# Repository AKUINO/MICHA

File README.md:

# MICHA
Modbus Interface to Control Heat and Actuators

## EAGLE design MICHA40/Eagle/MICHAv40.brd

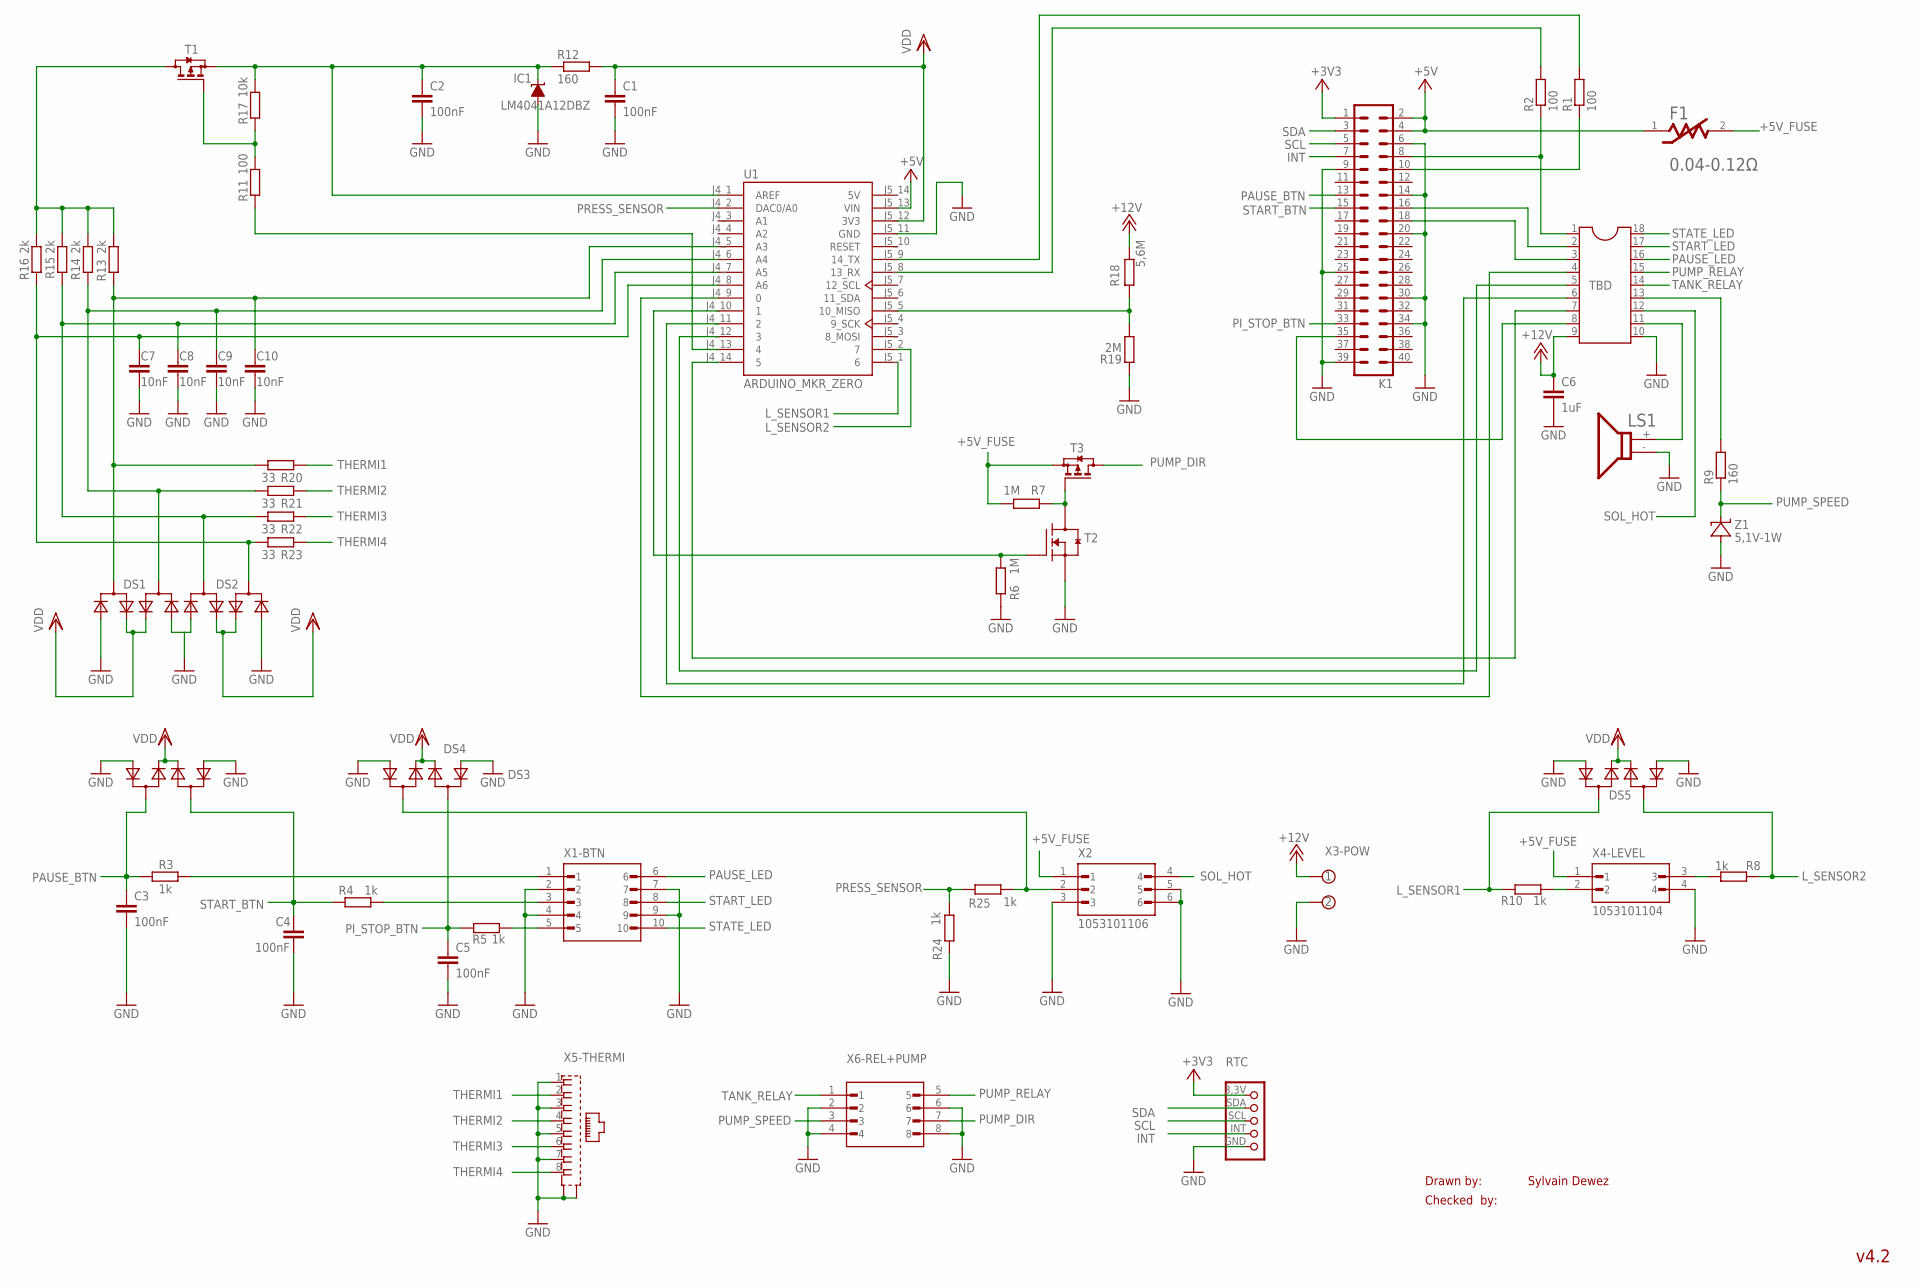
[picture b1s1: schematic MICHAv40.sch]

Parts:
C1, C2, C3, C4, C5: 100nF; C1206
C6: 1uF; C1206
C7, C8, C9, C10: 10nF; C1206
DS1, DS2, DS3, DS4, DS5: CMXSH2-4LSTRPBFREE
F1: LITTELFUSE_INC_1206L150THWRLITTELFUSE_INC_1206L15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; LITTELFUSE_INC_1206L150THWR_0
IC1: LM4041A12DBZ; DBZ_R-PDSO-G3
K1: PIN20X2; PIN_20X2
LS1: RSPRO-BUZZER-7800743
R1, R2, R11: 100; R1206
R3, R4, R5, R8, R10, R24, R25: 1k; R1206
R6, R7: 1M; R1206
R9, R12: 160; R1206
R13, R14, R15, R16: 2k; R1206
R17: 10k; R1206
R18: 5,6M; R1206
R19: 2M; R1206
R20, R21, R22, R23: 33; R1206
RTC: ODROID_C4_RTC_SHIELD
T1, T3: BSS84; SOT23
T2: MOSFET-NCH_SOT-23; SOT95P280X135-3N
TBD: DIL18S; SOCKET-18
U1: ARDUINO_MKR_ZERO; MODULE_ARDUINO_MKR_ZERO
X1-BTN: 1053101110; MOLEX_1053101110
X2: 1053101106; MOLEX_1053101106
X3-POW: BUCHANAN_2_3.2MM; BUCHANAN_2_3.5MM
X4-LEVEL: 1053101104; MOLEX_1053101104
X5-THERMI: SS-7188S-A-NF_V2; BEL_SS-7188S-A-NF
X6-REL+PUMP: 1053101108; MOLEX_1053101108
Z1: 5,1V-1W; ZENER_SMA

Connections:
5V: U1.J5_14 (5V)
+3V3: K1.1, RTC.3,3V (1)
+5V: F1.1, K1.2, K1.4, U1.J5_13 (VIN)
+5V_FUSE: F1.2, R7.2, T3.2 (S), X2.1, X4-LEVEL.1
+12V: C6.1, R18.2, TBD.9, X3-POW.1 (KL)
BLACKOUT: R18.1, R19.2, U1.J5_5 (10_MISO)
BTN_PAUSE: R3.2, X1-BTN.1
BTN_START: R4.2, X1-BTN.3
BTN_STOP: R5.2, X1-BTN.5
D0: TBD.4, U1.J4_9 (0)
D1: R6.2, T2.1 (G), U1.J4_10 (1)
D2: TBD.6, U1.J4_11 (2)
D3: TBD.5, U1.J4_12 (3)
D5: TBD.7, U1.J4_14 (5)
D21: R11.1, U1.J4_13 (4)
GND: C1.2, C2.2, C3.2, C4.2, C5.2, C6.2, C7.2, C8.2, C9.2, C10.2, DS1.1 (A3), DS1.6 (A2), DS2.1 (A3), DS2.6 (A2), DS3.1 (A3), DS3.6 (A2), DS4.1 (A3), DS4.6 (A2), DS5.1 (A3), DS5.6 (A2), IC1.2 (A), K1.6, K1.9, K1.14, K1.20, K1.25, K1.30, K1.34, K1.39, LS1.- (2), R6.1, R19.1, R24.1, RTC.GND (5), T2.2 (S), TBD.10, U1.J5_11 (GND), X1-BTN.2, X1-BTN.4, X1-BTN.7, X1-BTN.9, X2.3, X2.5, X2.6, X3-POW.2 (KL1), X4-LEVEL.4, X5-THERMI.1, X5-THERMI.3, X5-THERMI.5, X5-THERMI.7, X5-THERMI.S1 (GND1), X5-THERMI.S2 (GND2), X6-REL+PUMP.2, X6-REL+PUMP.4, X6-REL+PUMP.6, X6-REL+PUMP.8, Z1.A
INT: K1.7, RTC.INT (4)
L_SENSOR1: DS5.5 (C), R10.1, U1.J5_1 (6)
L_SENSOR2: DS5.2 (C1), R8.1, U1.J5_2 (7)
unnamed: R9.2, TBD.13
unnamed: R11.2, R17.1, T1.1 (G)
unnamed: C2.1, IC1.1 (C), R12.1, R17.2, T1.2 (S), U1.J4_1 (AREF)
unnamed: R13.1, R14.1, R15.1, R16.1, T1.3 (D)
unnamed: C10.1, DS1.2 (C1), R13.2, R20.1, U1.J4_5 (A3)
unnamed: C9.1, DS1.5 (C), R14.2, R21.1, U1.J4_6 (A4)
unnamed: C8.1, DS2.2 (C1), R15.2, R22.1, U1.J4_7 (A5)
unnamed: C7.1, DS2.5 (C), R16.2, R23.1, U1.J4_8 (A6)
unnamed: LS1.+ (1), TBD.11
unnamed: R7.1, T2.3 (D), T3.1 (G)
PAUSE_BTN: C3.1, DS3.5 (C), K1.13, R3.1
PAUSE_LED: TBD.16, X1-BTN.6
PI16: K1.16, TBD.2
PI18: K1.18, TBD.3
PI33: K1.35, TBD.8
PI_STOP_BTN: C5.1, DS4.2 (C1), K1.33, R5.1
PRESS_SENSOR: R24.2, R25.1, U1.J4_2 (DAC0/A0)
PUMP_DIR: T3.3 (D), X6-REL+PUMP.7
PUMP_RELAY: TBD.15, X6-REL+PUMP.5
PUMP_SPEED: R9.1, X6-REL+PUMP.3, Z1.C
RX_A: R2.2, U1.J5_8 (13_RX)
RX_PI: K1.10, R1.1
SCL: K1.5, RTC.SCL (3)
SDA: K1.3, RTC.SDA (2)
SENSOR: DS4.5 (C), R25.2, X2.2
SENSOR1: R10.2, X4-LEVEL.2
SENSOR2: R8.2, X4-LEVEL.3
SOL_HOT: TBD.12, X2.4
START_BTN: C4.1, DS3.2 (C1), K1.15, R4.1
START_LED: TBD.17, X1-BTN.8
STATE_LED: TBD.18, X1-BTN.10
TANK_RELAY: TBD.14, X6-REL+PUMP.1
THERMI1: R20.2, X5-THERMI.2
THERMI2: R21.2, X5-THERMI.4
THERMI3: R22.2, X5-THERMI.6
THERMI4: R23.2, X5-THERMI.8
TX_A: R1.2, U1.J5_9 (14_TX)
TX_PI: K1.8, R2.1, TBD.1
VDD: C1.1, DS1.3 (A4), DS1.4 (A1), DS2.3 (A4), DS2.4 (A1), DS3.3 (A4), DS3.4 (A1), DS4.3 (A4), DS4.4 (A1), DS5.3 (A4), DS5.4 (A1), R12.2, U1.J5_12 (3V3)

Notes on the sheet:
Drawn by:
Checked by:
Sylvain Dewez
v4.2

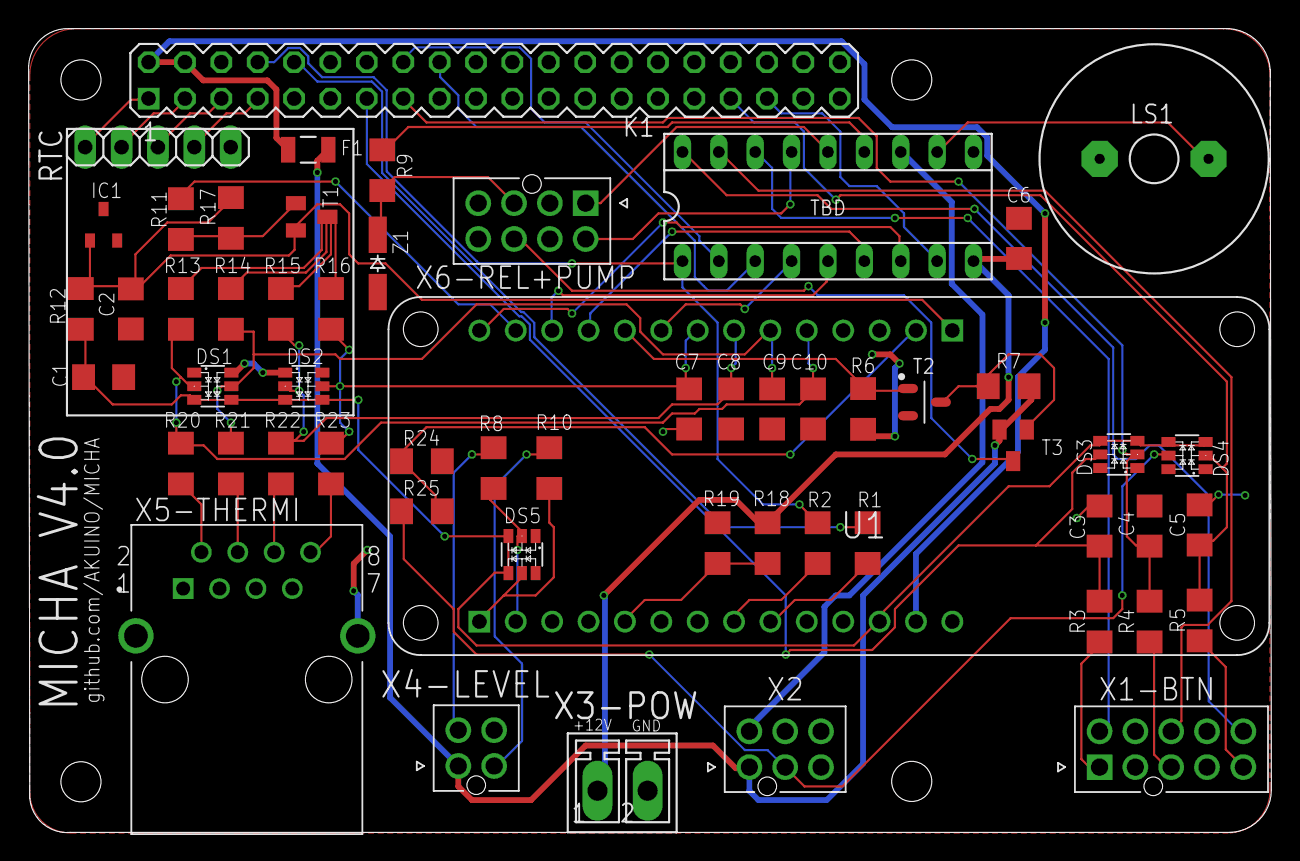
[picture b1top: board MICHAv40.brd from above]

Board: 2 copper layers, 86.8 x 56.1 mm, 57 parts (0 on the bottom side), 57 nets.

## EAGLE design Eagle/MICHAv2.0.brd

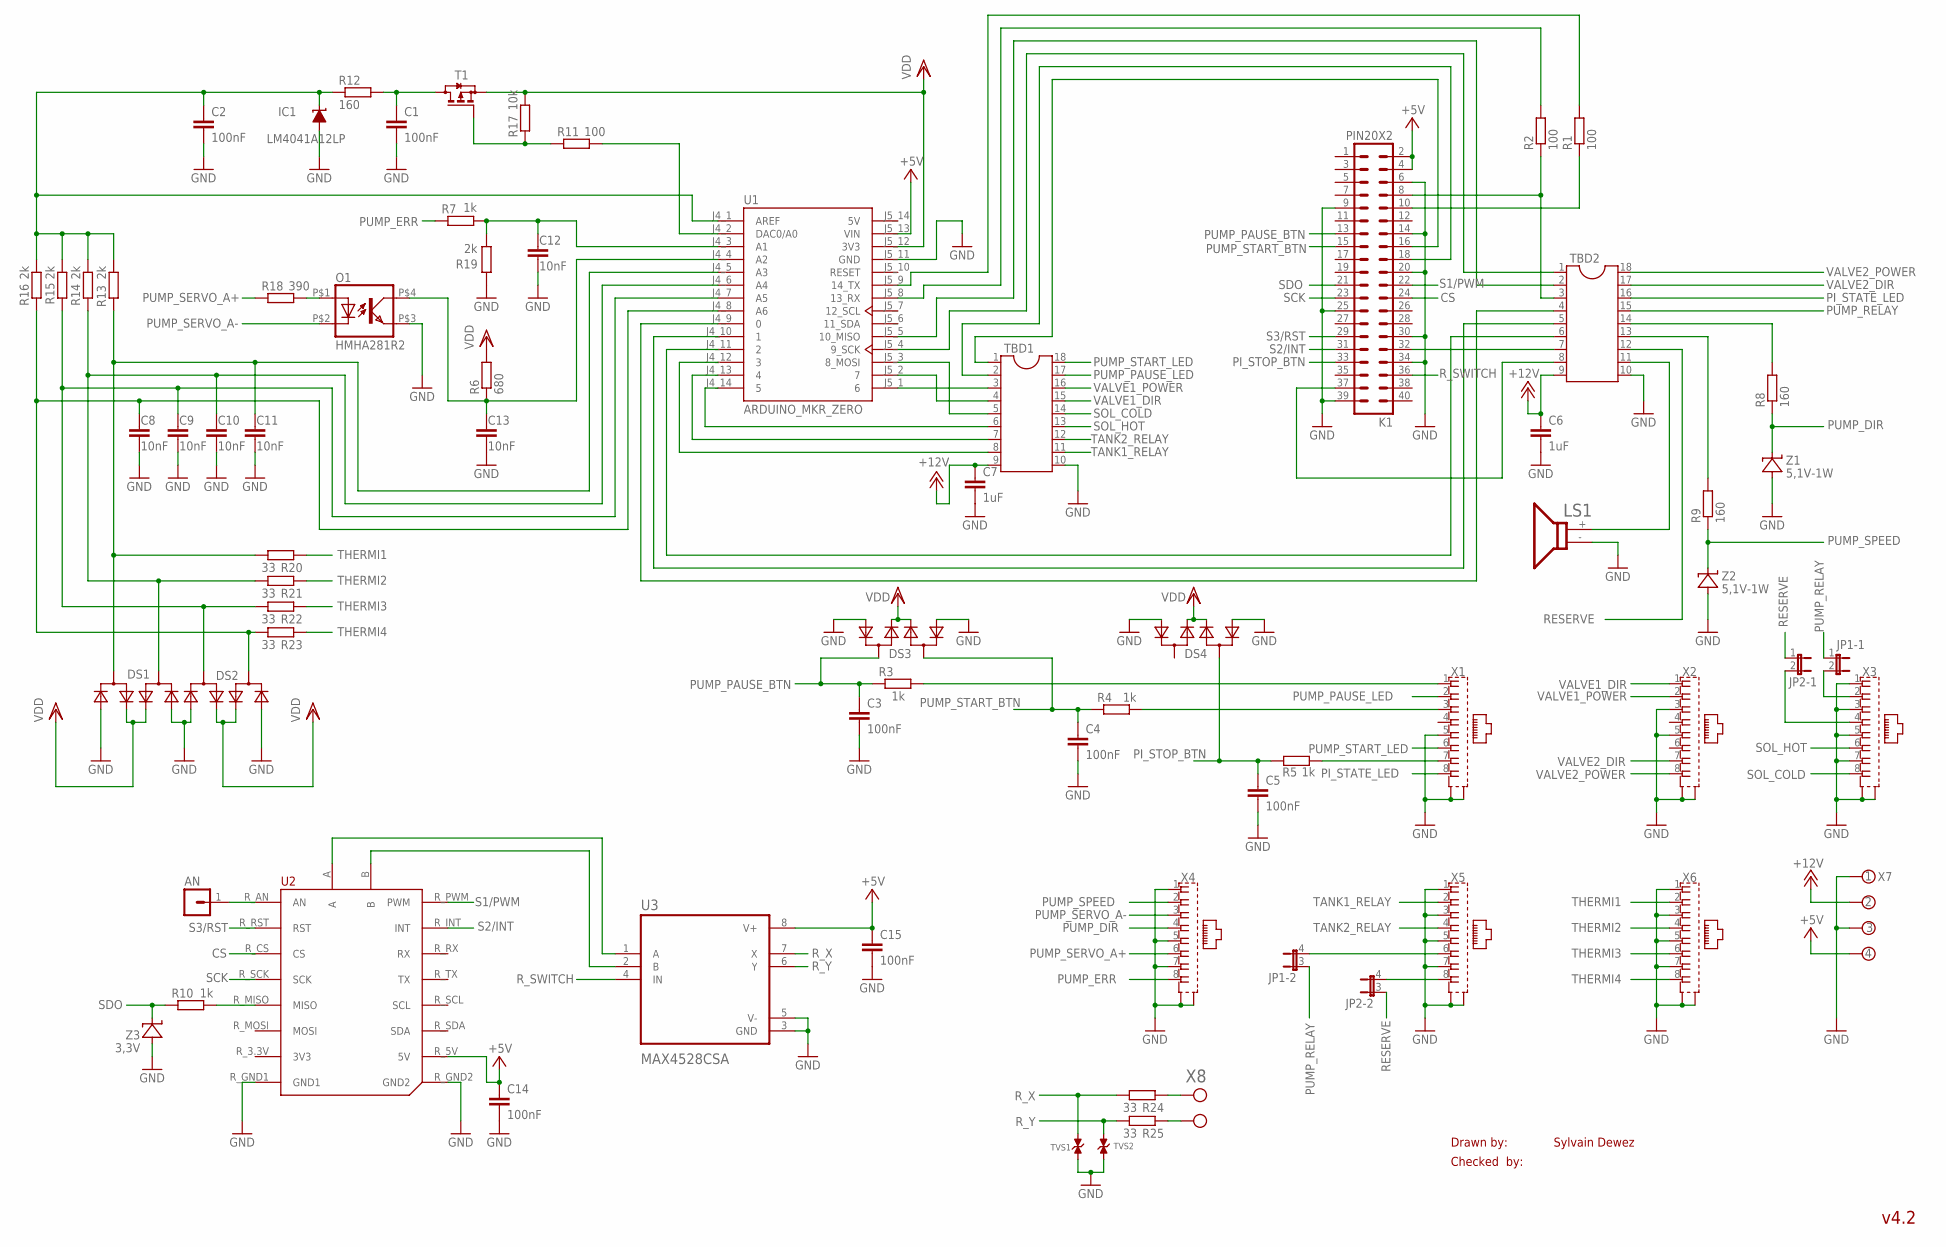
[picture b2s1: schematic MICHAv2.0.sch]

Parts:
AN: MA01_PINHEADER; MA01
C1, C2, C3, C4, C5, C14, C15: 100nF; C1206
C6, C7: 1uF; C1206
C8, C9, C10, C11, C12, C13: 10nF; C1206
DS1, DS2, DS3, DS4: SDM10M45SD; SDM10M45SD_SOT-26
IC1: LM4041A12LP; LP_O-PBCY-W3
JP1, JP2: JP2QE; JP2Q
K1: PIN20X2; PIN_20X2
LS1: RSPRO-BUZZER-7800743
O1: HMHA281R2
R1, R2, R11: 100; R1206
R3, R4, R5, R7, R10: 1k; R1206
R6: 680; R1206
R8, R9, R12: 160; R1206
R13, R14, R15, R16, R19: 2k; R1206
R17: 10k; R1206
R18: 390; R1206
R20, R21, R22, R23, R24, R25: 33; R1206
T1: BSS84; SOT23
TBD1, TBD2: DIL18S; SOCKET-18
TVS1, TVS2: TVS_SOD123
U1: ARDUINO_MKR_ZERO; MODULE_ARDUINO_MKR_ZERO
U2: MIKROE_CLICK_UPGRADE; MIKROE_BUS_MIDI_UPGRADE
U3: MAX4528CSA; SOIC127P600X175-8N
X1, X2, X3, X4, X5, X6: SS-7188S-A-NF_V2; BEL_SS-7188S-A-NF
X7: BUCHANAN_4_3.5MM
X8: MPT_0,5/_2-2,54_1725656_2; PH_MPT_0,5/_2-2,54_1725656
Z1, Z2: 5,1V-1W; ZENER_SMA
Z3: 3,3V; ZENER_SMA

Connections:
5V: U1.J5_14 (5V)
+5V: C14.1, C15.1, K1.2, K1.4, U1.J5_13 (VIN), U2.R_5V (5V), U3.8 (V+), X7.4 (KL3)
+12V: C6.1, C7.1, TBD1.9, TBD2.9, X7.2 (KL1)
CS: K1.24, U2.R_CS (CS)
D0: TBD2.4, U1.J4_9 (0)
D1: TBD2.5, U1.J4_10 (1)
D2: TBD2.6, U1.J4_11 (2)
D3: TBD1.8, U1.J4_12 (3)
D4: TBD1.7, U1.J4_13 (4)
D5: TBD1.6, U1.J4_14 (5)
D6: TBD1.3, U1.J5_1 (6)
D7: TBD1.4, U1.J5_2 (7)
D8: TBD1.5, U1.J5_3 (8_MOSI)
D9: TBD2.1, U1.J5_4 (9_SCK)
D10: TBD2.2, U1.J5_5 (10_MISO)
D19: C12.1, R7.2, R19.2, U1.J4_3 (A1)
D21: R11.2, U1.J4_2 (DAC0/A0)
GND: C1.2, C2.2, C3.2, C4.2, C5.2, C6.2, C7.2, C8.2, C9.2, C10.2, C11.2, C12.2, C13.2, C14.2, C15.2, DS1.1 (A2), DS1.4 (A3), DS2.1 (A2), DS2.4 (A3), DS3.1 (A2), DS3.4 (A3), DS4.1 (A2), DS4.4 (A3), IC1.3 (A), K1.6, K1.9, K1.14, K1.20, K1.25, K1.30, K1.34, K1.39, LS1.- (2), O1.P$3 (EMIT), R19.1, TBD1.10, TBD2.10, TVS1.P$2 (C1), TVS2.P$2 (C1), U1.J5_11 (GND), U2.R_GND1 (GND1), U2.R_GND2 (GND2), U3.3 (GND), U3.5 (V-), X1.5, X1.S1 (GND1), X1.S2 (GND2), X2.3, X2.5, X2.S1 (GND1), X2.S2 (GND2), X3.1, X3.3, X3.5, X3.7, X3.S1 (GND1), X3.S2 (GND2), X4.1, X4.5, X4.7, X4.S1 (GND1), X4.S2 (GND2), X5.1, X5.3, X5.5, X5.7, X5.S1 (GND1), X5.S2 (GND2), X6.1, X6.3, X6.5, X6.7, X6.S1 (GND1), X6.S2 (GND2), X7.1 (KL), X7.3 (KL2), Z1.A, Z2.A, Z3.A
unnamed: U2.B, U3.2 (B)
unnamed: R9.2, TBD2.13
unnamed: R11.1, R17.1, T1.1 (G)
unnamed: R8.2, TBD2.14
unnamed: R4.2, X1.3
unnamed: C2.1, IC1.2 (C), R12.1, R13.1, R14.1, R15.1, R16.1, U1.J4_1 (AREF)
unnamed: O1.P$1 (A), R18.2
unnamed: C1.1, R12.2, T1.3 (D)
unnamed: C13.1, O1.P$4 (COL), R6.1, U1.J4_4 (A2)
unnamed: U2.A, U3.1 (A)
unnamed: C11.1, DS1.3 (C1), R13.2, R20.1, U1.J4_5 (A3)
unnamed: C10.1, DS1.6 (C), R14.2, R21.1, U1.J4_6 (A4)
unnamed: C9.1, DS2.3 (C1), R15.2, R22.1, U1.J4_7 (A5)
unnamed: C8.1, DS2.6 (C), R16.2, R23.1, U1.J4_8 (A6)
unnamed: R10.2, U2.R_MISO (MISO)
unnamed: AN.1, U2.R_AN (AN)
unnamed: R24.2, X8.2 (KL1)
unnamed: R25.2, X8.1 (KL)
unnamed: JP1.4 (2), X5.6
unnamed: JP1.2, X3.2
unnamed: JP2.4 (2), X5.8
unnamed: JP2.2, X3.4
unnamed: R3.2, X1.1
unnamed: R5.2, X1.7
unnamed: LS1.+ (1), TBD2.11
PI16: K1.16, TBD1.1
PI18: K1.18, TBD1.2
PI32: K1.32, TBD2.7
PI33: K1.37, TBD2.8
PI_STATE_LED: TBD2.16, X1.8
PI_STOP_BTN: C5.1, DS4.3 (C1), K1.33, R5.1
PUMP_DIR: R8.1, X4.4, Z1.C
PUMP_ERR: R7.1, X4.8
PUMP_PAUSE_BTN: C3.1, DS3.6 (C), K1.13, R3.1
PUMP_PAUSE_LED: TBD1.17, X1.2
PUMP_RELAY: JP1.1, JP1.3 (1), TBD2.15
PUMP_SERVO_A+: R18.1, X4.6
PUMP_SERVO_A-: O1.P$2 (C), X4.3
PUMP_SPEED: R9.1, X4.2, Z2.C
PUMP_START_BTN: C4.1, DS3.3 (C1), K1.15, R4.1
PUMP_START_LED: TBD1.18, X1.6
RESERVE: JP2.1, JP2.3 (1), TBD2.12
RX_A: R2.2, U1.J5_8 (13_RX)
RX_PI: K1.10, R1.1
R_SWITCH: K1.36, U3.4 (IN)
R_X: R24.1, TVS1.P$1 (C), U3.7 (X)
R_Y: R25.1, TVS2.P$1 (C), U3.6 (Y)
S1/PWM: K1.22, U2.R_PWM (PWM)
S2/INT: K1.31, U2.R_INT (INT)
S3/RST: K1.29, U2.R_RST (RST)
SCK: K1.23, U2.R_SCK (SCK)
SDO: K1.21, R10.1, Z3.C
SOL_COLD: TBD1.14, X3.8
SOL_HOT: TBD1.13, X3.6
TANK1_RELAY: TBD1.11, X5.2
TANK2_RELAY: TBD1.12, X5.4
THERMI1: R20.2, X6.2
THERMI2: R21.2, X6.4
THERMI3: R22.2, X6.6
THERMI4: R23.2, X6.8
TX_A: R1.2, U1.J5_9 (14_TX)
TX_PI: K1.8, R2.1, TBD2.3
VALVE1_DIR: TBD1.15, X2.1
VALVE1_POWER: TBD1.16, X2.2
VALVE2_DIR: TBD2.17, X2.7
VALVE2_POWER: TBD2.18, X2.8
VDD: DS1.2 (A1), DS1.5 (A4), DS2.2 (A1), DS2.5 (A4), DS3.2 (A1), DS3.5 (A4), DS4.2 (A1), DS4.5 (A4), R6.2, R17.2, T1.2 (S), U1.J5_12 (3V3)

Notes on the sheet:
Drawn by:
Checked by:
Sylvain Dewez
v4.2

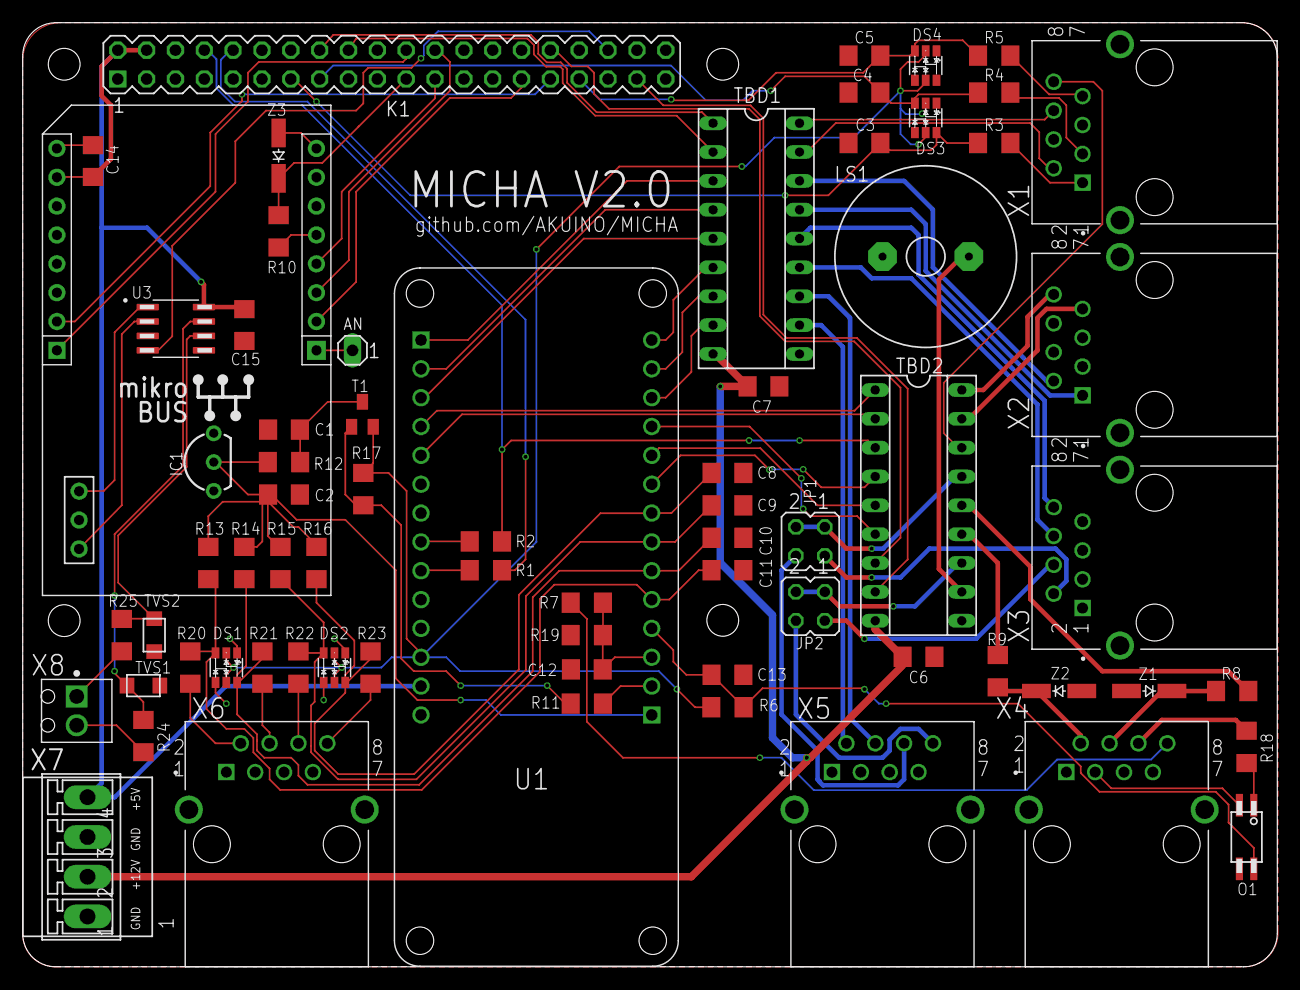
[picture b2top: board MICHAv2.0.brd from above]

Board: 2 copper layers, 110.5 x 83.1 mm, 70 parts (0 on the bottom side), 84 nets.

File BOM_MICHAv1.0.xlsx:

|  |  |  |  |  | En stock | Peut être remplacé par valeur en stock
Item | Schematics Ref | Component | Value | Qty | Ref | Packaging | Remarques | Liens
1 | C1-C5, C14-C15 | Condensateur tantal | 100nF | 7 | T491A104K035AT | 1206 (3216 métrique) |  | https://www.tme.eu/fr/katalog/condensateurs-au-tantale-smd_1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
2 | C6-C7 | Condensateur céramique | 1µF | 2 | C1206C105M4RACTU | 1206 (3216 métrique) |  | https://www.tme.eu/be/fr/details/c1206c105m4ractu/condensate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
3 | C8-C13 | Condensateur céramique | 10nF | 6 | C1206C103J1RACTU | 1206 (3216 métrique) |  | https://www.tme.eu/be/fr/details/c1206c103j1ractu/condensate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
 |  |  |  |  | C1206C103JCGACAUTO |  |  | https://befr.rs-online.com/web/p/mlccs-multilayer-ceramic-ca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
4 | D1 | Diode | 0,26V | 1 | STPS1L30A | SMA | Vs = 0,26V, Shottky | https://www.tme.eu/be/fr/details/stps1l30a/diodes-schottky-s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
 |  |  |  |  | STPS1L30A |  |  | https://befr.rs-online.com/web/p/schottky-diodes-rectifiers/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
5 | IC1 | Référentiel de tension | 2,5V | 1 | LM4040AIZ-2.5/NOPB | TO-92 | +-0,1% | https://befr.rs-online.com/web/p/voltage-references/5343037/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
6 | K1 | Connecteur | 2*20 | 1 | 2202982 | traversant | GPIO Header pour Raspberry | https://befr.rs-online.com/web/p/enclosure-accessories/12243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
7 | LS1 | Buzzer | 12V | 1 | 780-0743 | Traversant |  | https://befr.rs-online.com/web/p/piezo-buzzer-components/7800743/
8 | R1-R2, R11 | Résistance | 100 | 3 | TC0625B1000T1E | 1206 (3216 métrique) | Rx et Tx et la gate du MOSFET | https://www.tme.eu/fr/details/tc0625b1000t1e/resistances-de-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
9 | R3-R5, R10 | Résistance | 1k | 4 | RN73H2BTTD1001B25 | 1206 (3216 métrique) |  | https://www.mouser.be/ProductDetail/KOA-Speer/RN73H2BTTD1001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
10 | R6-R7, R13-R16 | Résistance | 2k | 6 | AR06BTCV2001 | 1206 (3216 métrique) | Tolérance: 0,1% | https://www.tme.eu/fr/details/ar1206-2k-0.1%25/resistances-d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
 |  |  |  |  | ERA8AEB202V |  |  | https://befr.rs-online.com/web/p/surface-mount-fixed-resisto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
11 | R8-R9, R12 | Résistance | 160 | 3 | 721-8093 | 1210 (3225 métrique) | 1/2W La valeur de R8-R9 doit être comprise entre 35 et 174 ohms, en privilégian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 | https://befr.rs-online.com/web/p/surface-mount-fixed-resisto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
12 | R17 | Résistance | 10k | 1 | AR06BTCV1002 | 1206 (3216 métrique) |  | https://www.tme.eu/fr/details/ar1206-10k-0.1%25/resistances-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
 |  |  |  |  | CRT1206-BY-1002ELF |  |  | https://befr.rs-online.com/web/p/surface-mount-fixed-resisto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
13 | T1 | Transistor |  | 1 | FDV304P | SOT23 | Commutateur d'excitation, canal P | https://www.tme.eu/fr/details/fdv304p/transistors-avec-canal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
 |  |  |  |  | FDV304P |  |  | https://befr.rs-online.com/web/p/mosfets/3544913/
14 | TBD1-TBD2 | Transistor Array |  | 2 | TBD62783APG | DIP18 | Canal N | https://www.mouser.be/ProductDetail/Toshiba/TBD62783APG/?qs=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
15 | TVS1-TVS3 | TVS | 5V/12pF | 3 | 824022 | SOT23-3L |  | https://www.mouser.be/ProductDetail/Wurth-Elektronik/824022/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
16 | U1 | µC |  | 1 | Arduino MKR Zero | Traversant
17 | U2 | R-Meter |  | 1 | R-Meter | Traversant |  | https://www.mikroe.com/r-meter-click
18 | X1-X6 | Connecteur | RJ45 | 6 | RJULE4318101 | Traversant | Connecteur RJ45 blindé | https://www.mouser.be/ProductDetail/amphenol/rjule4318101/?q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
19 | X7 | Connecteur | Bornier 4 voies | 1 | 2351886-4 | Traversant | Pas de 3,5mm, vertical, mâle, détrompeur | https://befr.rs-online.com/web/p/pcb-terminal-blocks/1951950/
 |  |  |  |  | 15EDGVC-3.5-04P-14-00A(H) |  |  | https://www.tme.eu/be/fr/details/15edgvc-3.5-04p/borniers-de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
20 | Z1-Z2 | Diode Zener | 5,1V | 2 | SMAZ5V1-13-F | SMA | 5,1V / 1W | https://www.tme.eu/be/fr/details/smaz5v1-13-f/diodes-zener-s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
 |  |  |  |  | SMAZ5V1-13-F |  |  | https://befr.rs-online.com/web/p/zener-diodes/7515054/
21 | Z3-Z5 | Diode Zener | 3,3V | 3 | 1SMA5913BT3G | SMA | 3,3V | https://www.tme.eu/be/fr/details/1sma5913bt3g/diodes-zener-s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
 |  |  |  |  | 1SMA5913BT3G |  |  | https://befr.rs-online.com/web/p/zener-diodes/7925338/
22 |  | Connecteur | Bornier 4 voies | 1 | 1840382 | Pluggable | Version femelle de X7, plug à vis | https://www.tme.eu/fr/details/mc1.5_4-st-3.5/borniers-de-ser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
23 |  | Connecteur | DIP18 | 2 | DS1009-18AT1NX | DIP18 | Support pour les TBD | https://www.tme.eu/fr/details/icvt-18p/supports-dip-standard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
 |  |  |  |  | AR 18 HZL-TT |  |  | https://befr.rs-online.com/web/p/dil-sockets/6742441/
24 |  | Connecteur | embase femelle 14 broches | 2 | DS1023-1*14S21 | Traversant | Pas de 2,54mm, pour placer l'Arduino MKR | https://www.tme.eu/be/fr/details/zl262-14sg/barres-et-socles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
 |  |  |  |  | SSW-114-01-T-S |  |  | https://befr.rs-online.com/web/p/pcb-sockets/1557926/
25 |  | Connecteur | embase femelle 8 broches | 2 |  | Traversant | Pas de 2,54mm, pour placer le R-Meter
26 |  | Bouton poussoir | 12V, vert | 1 | VAQ-9-10-12-G | Sur boitier | Bouton poussoir à Led verte 12V | https://www.tme.eu/fr/details/vaq-9-10-12-g/commutateurs-sta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
27 |  | Bouton poussoir | 12V, rouge | 1 | VAQ-9-10-12-R | Sur boitier | Bouton poussoir à Led verte 12V | https://www.tme.eu/fr/details/vaq-9-10-12-r/commutateurs-sta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
28 |  | Bouton poussoir | 12V, jaune | 1 | VAQ-9-10-12-Y | Sur boitier | Bouton poussoir à Led verte 12V | https://www.tme.eu/fr/details/vaq-9-10-12-y/commutateurs-sta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
29 |  | Raspberry |  | 1 | Raspberry Pi 3 B+
30 |  | Thermistance | NTC | 4 | GA10K4A1A | Traversant
31 |  | Câble | Ethernet F/FTP ou S/FTP | 5
32 |  | One-Wire USB |  | 1 |  | USB
33 |  | Capteur One-Wire |  | 3 |  | One-Wire
34 |  | Joint passe câble |  | 7 |  | Sur boitier |  | https://www.icotek.com/fr/produits/joints-passe-cable/kt-gy
35 |  | Presse-étoupes |  | 7 |  | Sur boitier |  | https://www.icotek.com/fr/produits/presse-etoupes/qvt

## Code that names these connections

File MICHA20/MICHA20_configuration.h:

// MICHA PROJECT
// Register and I/O configuration
// For Arduino MKR Zero

#define VERSION 2 // version of the current PCB


// constants
#define ID  1                 // default modbus ID
uint16_t speed_step = 400;    // default speed Hz decrease/increase
boolean debug_flag = false;   // debug mode enable flag (with debug_flag false, less Serial.print, better timing...)
// ms Delay after startup before Setup
#define SETUP_DELAY 1000
// Modbus serial speed
#define BAUD_RATE 19200


// configuration of the relative register adresses
// coils
#define THERMIS_POW_REG                   0x01   // register which stores the thermistor power state
#define PUMP_DIR_REG                      0x10   // register which stores the pump direction
#define PUMP_POW_REG                      0x11   // register which stores the pump power state
#define TANK1_REG                         0x20   // register which stores the tank 1 state
#define TANK2_REG                         0x21   // register which stores the tank 2 state
#define SOL_HOT_REG                       0x30   // register which stores the hot water solenoid state
#define SOL_COLD_REG                      0x31   // register which stores the cold water solenoid state
#define VALVE1_POW_REG                    0x32   // register which stores the valve 1 power state
#define VALVE1_DIR_REG                    0x33   // register which stores the valve 1 direction
#define VALVE2_POW_REG                    0x34   // register which stores the valve 2 power state
#define VALVE2_DIR_REG                    0x35   // register which stores the valve 2 direction
#define BOOT_FLAG_REG                     0x40   // register which stores the boot state
#define DEBUG_FLAG_REG                    0x41   // register which stores the debug state
// input registers
#define GEN_STATE_REG                     0x00   // register which stores the general state of the system
#define THERMI1_REG                       0x01   // register which stores the thermistor 1 value (0 - 4095)
#define THERMI2_REG                       0x02   // register which stores the thermistor 2 value (0 - 4095)
#define THERMI3_REG                       0x03   // register which stores the thermistor 3 value (0 - 4095)
#define THERMI4_REG                       0x04   // register which stores the thermistor 4 value (0 - 4095)
#define PUMP_ERR_REG                      0x10   // register which stores the error code returned by the pump regulator
#define PUMP_SERVO_PERIODMAX_REG          0x11   // register which stores the max period of the servo signal returned by the pump
#define PUMP_SERVO_PERIODMIN_REG          0x12   // register which stores the min period of the servo signal returned by the pump
#define PUMP_SERVO_PERIODAVG_REG          0x13   // register which stores the period average of the servo signal returned by the pump (on some time)
#define PUMP_SERVO_PERIODSTDDEV_REG       0x14   // register which stores the period standard deviation of the servo signal returned by the pump  (on some time)
#define ERROR_CODE_REG                    0x20   // register which stores the general error codes
// holding registers
#define ID_REG                            0x00   // register which stores the modbus ID
#define PUMP_SPEED_REG                    0x10   // register which stores the pump speed
#define PUMP_SPEED_INC_REG                0x11   // register which stores the increasing/decreasing value of the pump frequency
#define PUMP_SPIN_RATE_REG                0x12   // register which stores the pump spining rate approved
#define PUMP_SERVO_PULSES_REG             0x13   // register which stores the pulse count of the servo signal returned by the pump (on some time)


// pin assignment
#if VERSION == 2
  #define THERMIS_POW_PIN       A0         // thermistor power pin
  #define PUMP_ERR_PIN          A1         // pump error signal pin
  #define PUMP_SERVO_PIN        17         // pump servo signal pin (A2)
  #define THERMI1_PIN           A3         // thermistor 1 pin
  #define THERMI2_PIN           A4         // thermistor 2 pin
  #define THERMI3_PIN           A5         // thermistor 3 pin
  #define THERMI4_PIN           A6         // thermistor 4 pin
  #define PUMP_POW_PIN          0          // pump power pin
#elif VERSION == 1
  #define THERMI1_PIN           A0         // thermistor 1 pin
  #define THERMI2_PIN           A1         // thermistor 2 pin
  #define THERMI3_PIN           A2         // thermistor 3 pin
  #define THERMI4_PIN           A3         // thermistor 4 pin
  #define THERMIS_POW_PIN       21         // thermistor power pin
  #define PUMP_ERR_PIN          19         // pump error signal pin
  #define PUMP_POW_PIN          20         // pump power pin   DO NOT USE FOR NOW
  #define PUMP_SERVO_PIN        0          // pump servo signal pin
#endif
// common pins
#define PUMP_DIR_PIN          1          // pump direction pin
#define PUMP_SPEED_PIN        2          // pump speed pin
#define TANK1_PIN             3          // tank 1 pin
#define TANK2_PIN             4          // tank 2 pin
#define SOL_HOT_PIN           5          // hot water solenoid pin
#define VALVE1_POW_PIN        6          // valve 1 power pin
#define VALVE1_DIR_PIN        7          // valve 1 direction pin
#define SOL_COLD_PIN          8          // cold water solenoid pin
#define VALVE2_POW_PIN        9          // valve 2 power pin
#define VALVE2_DIR_PIN        10         // valve 2 direction pin

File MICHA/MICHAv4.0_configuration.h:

// MICHA PROJECT
// Register and I/O configuration
// For Arduino MKR Zero


// settings
#define VERSION 4             // version of the current PCB
#define ID  1                 // default modbus ID
#define SETUP_DELAY 1000      // ms Delay after startup before Setup
#define BAUD_RATE 19200       // Modbus serial speed
boolean debug_flag = false;   // debug mode enable flag (with debug_flag false, less Serial.print, better timing...)
boolean level1_flag = false;  // allow to enable/disable the level 1 sensor management, i.e. the input level monitoring (0 = disable)
boolean level2_flag = false;  // allow to enable/disable the level 2 sensor management, i.e. the output level monitoring (0 = disable)
boolean press_flag = false;   // allow to enable/disable the pressure sensor management (0 = disable)
uint16_t speed_step = 400;    // default speed Hz decrease/increase




// configuration of the relative register adresses
// coils / output coils
#define THERMIS_POW_REG                   0x00   // register which stores the thermistor power state
#define LEVEL1_FLAG_REG                   0x01   // register which stores the flag which enables/disables the level 1 sensor management
#define LEVEL2_FLAG_REG                   0x02   // register which stores the flag which enables/disables the level 2 sensor management
#define PRESS_FLAG_REG                    0x03   // register which stores the flag which enables/disables the pressure sensor management
#define PUMP_DIR_REG                      0x10   // register which stores the pump direction
#define PUMP_POW_REG                      0x11   // register which stores the pump power state
#define TANK1_REG                         0x20   // register which stores the tank 1 state
#define SOL_HOT_REG                       0x30   // register which stores the hot water solenoid state
#define BOOT_FLAG_REG                     0x40   // register which stores the boot state
#define DEBUG_FLAG_REG                    0x41   // register which stores the debug state
// input bits / discrete inputs
#define LEVEL_SENSOR1_REG                 0x01   // register which stores the state of the input level sensor (1 for water)
#define LEVEL_SENSOR2_REG                 0x02   // register which stores the state of the output level sensor (1 for water)
#define EMERGENCY_STOP_REG                0x10   // register which stores the state of  the emergency stop button (0 for active emergency stop)
// input registers
#define GEN_STATE_REG                     0x00   // register which stores the general state of the system
#define THERMI1_REG                       0x01   // register which stores the thermistor 1 value (0 (high temp) - 4095 (low temp))
#define THERMI2_REG                       0x02   // register which stores the thermistor 2 value (0 (high temp) - 4095 (low temp))
#define THERMI3_REG                       0x03   // register which stores the thermistor 3 value (0 (high temp) - 4095 (low temp))
#define THERMI4_REG                       0x04   // register which stores the thermistor 4 value (0 (high temp) - 4095 (low temp))
#define PRESS_SENSOR_REG                  0x10   // register which stores the pressure sensor value (0 (low pressure) - 4095 (high pressure))
#define ERROR_CODE_REG                    0x20   // register which stores the general error codes
// holding registers
#define ID_REG                            0x00   // register which stores the modbus ID
#define PUMP_SPEED_REG                    0x10   // register which stores the pump speed
#define PUMP_SPEED_INC_REG                0x11   // register which stores the increasing/decreasing value of the pump frequency


// pin assignment
#if VERSION == 4
  #define PRESS_SENSOR_PIN      A0         // pressure sensor input pin (0 (low pressure) - 4095 (high pressure))
  #define THERMI1_PIN           A3         // thermistor 1 input pin (0 (high temp) - 4095 (low temp))
  #define THERMI2_PIN           A4         // thermistor 2 input pin (0 (high temp) - 4095 (low temp))
  #define THERMI3_PIN           A5         // thermistor 3 input pin (0 (high temp) - 4095 (low temp))
  #define THERMI4_PIN           A6         // thermistor 4 input pin (0 (high temp) - 4095 (low temp))
  #define PUMP_POW_PIN          0          // pump power pin
  #define PUMP_DIR_PIN          1          // pump direction pin
  #define PUMP_SPEED_PIN        2          // pump speed pin
  #define TANK1_PIN             3          // tank 1 pin
  #define THERMIS_POW_PIN       4          // thermistor power pin
  #define SOL_HOT_PIN           5          // hot water solenoid pin
  #define LEVEL_SENSOR1_PIN     6          // level sensor 1 input pin
  #define LEVEL_SENSOR2_PIN     7          // level sensor 2 input pin
  #define EMERGENCY_STOP_PIN    10         // emergency stop input pin (0 for active emergency stop)
#endif

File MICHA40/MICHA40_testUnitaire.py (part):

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# Odroid configuration
GPIO.setmode(GPIO.BOARD)
# pin used
START_BTN_PIN               = 15    # pin on which the start button is connected
PAUSE_BTN_PIN               = 13    # pin on which the pause button is connected
STOP_BTN_PIN                = 33    # pin on which the start button is connected
START_LED_PIN               = 16    # pin on which the start led is connected
PAUSE_LED_PIN               = 18    # pin on which the pause led is connected
STATE_LED_PIN               = 8     # pin on which the state led is connected
BUZZER_PIN                  = 35    # pin on which the buzzer is connected
# pin configuration
GPIO.setup(START_BTN_PIN, GPIO.IN)
GPIO.setup(PAUSE_BTN_PIN, GPIO.IN)
GPIO.setup(STOP_BTN_PIN, GPIO.IN)
GPIO.pinMode(STOP_BTN_PIN, GPIO.PUD_UP)
GPIO.setup(START_LED_PIN, GPIO.OUT)
GPIO.setup(PAUSE_LED_PIN, GPIO.OUT)
GPIO.setup(STATE_LED_PIN, GPIO.OUT)
GPIO.setup(BUZZER_PIN, GPIO.OUT)

# Registre configuration
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        self.boot_flag = 1
        self.thermi = 0
        self.thermis_pow = 0
        self.pump_speed = 0
        self.pump_speed_inc = 0
        self.pump_dir = 0
        self.pump_power = 0
        self.tank1 = 0
        self.sol_hot = 0
        self.general_state = 0
        self.error_code = 0
        self.debug_flag = 0
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        return self.pump_power
    
    def get_pump_dir(self): # to get the direction state of the pump (stored in the register), returns the pump direction value
        self.pump_dir = self.read_pin(PUMP_DIR_REG)
        return self.pump_dir
    
    def get_pump_speed(self): # to get the speed of the pump (stored in the register), returns the pump speed
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        return 0
    
    def get_sol_hot(self): # to get the state of the hot water solenoid (stored in the register)
        self.sol_hot = self.read_pin(SOL_HOT_REG)
        return self.sol_hot

    def get_level1_sensor(self): # to get the level 1 sensor value, returns the level 1 sensor value
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        return 0
        
    def get_startBtn(self): # to get the state of the start button
        return GPIO.digitalRead(START_BTN_PIN)
    
    def get_pauseBtn(self): # to get the state of the pause button
        return GPIO.digitalRead(PAUSE_BTN_PIN)
    
    def get_stopBtn(self): # to get the state of the start button
        return GPIO.digitalRead(STOP_BTN_PIN)
        
    def get_startLed(self):
        return GPIO.digitalRead(START_LED_PIN)
        
    def set_startLed(self, state=0):
        GPIO.output(START_LED_PIN, state)
        return 0
    
    def get_pauseLed(self):
        return GPIO.digitalRead(PAUSE_LED_PIN)
        
    def set_pauseLed(self, state=0):
        GPIO.output(PAUSE_LED_PIN, state)
        return 0
        
    def get_stateLed(self):
        return GPIO.digitalRead(STATE_LED_PIN)
        
    def set_stateLed(self, state=0):
        GPIO.output(STATE_LED_PIN, state)
        return 0
    def get_buzzer(self):
        return GPIO.digitalRead(BUZZER_PIN)
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    def pressSensor(choice):
        """Get or set a value related to the pressure sensor."""
        
        Vcc = 5 # power voltage applied to the pressure sensor
        pressure = pasto.get_press_sensor() # raw value of the pressure (0-4095)
        pressure_V = pressure/1638 # pressure in V
        pressure_psi = 125*(pressure_V/Vcc)-12.5 # pressure in Psi
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
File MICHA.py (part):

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        self.device = device
        self.boot_flag = 1
        self.thermi = 0
        self.pump_speed = 0
        self.pump_dir = 0
        self.pump_power = 0
        self.tank1 = 0
        self.tank2 = 0
        self.sol_hot = 0
        self.sol_cold = 0
        self.valve1_power = 0
        self.valve1_dir = 0
        self.valve2_power = 0
        self.valve2_dir = 0
        self.general_state = 0
        self.error_code = 0
        self.debug_flag = 0
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        return self.pump_power
    
    def get_pump_dir(self): # to get the direction state of the pump (stored in the register), returns the pump direction value
        self.pump_dir = self.read_pin(PUMP_DIR_REG)
        return self.pump_dir
    
    def get_pump_speed(self): # to get the speed of the pump (stored in the register), returns the pump speed
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        return 0
    
    def get_sol_hot(self): # to get the state of the hot water solenoid (stored in the register)
        self.sol_hot = self.read_pin(SOL_HOT_REG)
        return self.sol_hot
    
    def get_sol_cold(self): # to get the state of the cold water solenoid (stored in the register)
        self.sol_cold = self.read_pin(SOL_COLD_REG)
        return self.sol_cold
    
    def set_valve1_power(self,power=0): # to set the power state of the valve 1
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        return 0
    
    def get_valve1_power(self): # to get the power state of the valve 1 (stored in the register)
        self.valve1_power = self.read_pin(VALVE1_POW_REG)
        return self.valve1_power
    
    def get_valve2_power(self): # to get the power state of the valve 2 (stored in the register)
        self.valve2_power = self.read_pin(VALVE2_POW_REG)
        return self.valve2_power
    
    def set_valve1_dir(self,dir=0): # to set the direction of the valve 1
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        return 0
    
    def get_valve1_dir(self): # to get the direction of the valve 1 (stored in the register)
        self.valve1_dir = self.read_pin(VALVE1_DIR_REG)
        return self.valve1_dir

    def get_valve2_dir(self): # to get the direction of the valve 2 (stored in the register)
        self.valve2_dir = self.read_pin(VALVE2_DIR_REG)
        return self.valve2_dir

    def get_general_state(self): # to get the general state of the system (stored in the register)
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
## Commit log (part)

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2021-03-27 premiers ajouts
2021-04-06 Renaming
    MICHA_v0.3.3 is renamed to MICHA to make it more general
2021-04-06 v1.0.0
    Update to version v1.0.0
2021-04-06 Register added
    Spinning error rate register added
2021-04-06 I/O update
    Switching between the speed pin and the power pin of the pump
2021-04-06 Renaming
2021-04-06 English version
2021-04-06 Update MICHA.py
    Add a self-test mode
2021-04-06 Library and standalone mode
2021-04-06 v1.0.0
2021-04-06 v1.0.1
2021-04-08 Update Structure registres modbus.docx
    Ajoit du registre "témoin de démarrage"
2021-04-08 v1.1.0
2021-04-08 Reboot management added
2021-04-08 thermistor value in mV
2021-04-09 Counting servo at each second
2021-04-12 Speed and power pump pins modified
    - Voltage tags on X7
    - Output valve names updated
2021-04-12 v1.1.1 (MICHA.ino)
    English version
2021-04-13 Pump servo pin updated
    Modification of the next pins:
    - Thermis power -> A0
    - Error pump -> A1
    - Servo pin -> A2
    - Thermi 1 -> A3
    - Thermi 2 -> A4
2021-04-14 v1.1.2
    - reading and decoding the pump error signal implemented (writing in register not yet implemented)
    - loop section reorganized
2021-04-16 PUMP_SERVO_PIN correction
    The name was wrong --> corrected
    Switching to input_pullup mode
2021-04-16 Poll pump error pin every 35 ms
2021-04-16 moins de delay
2021-04-16 Interrupt for Servo
2021-04-21 v1.1.3 - pump servo registers updated
2021-04-21 Pump servo registers updated
2021-04-22 Mac synchronization
2021-04-22 interrupt servo test
    Test codes to count the pulse number and the period of the pump servo signal
2021-04-22 Average
2021-04-22 update micro
2021-04-22 Tests
2021-04-23 Delete schéma projet global.jpg
    Merge the same file ames
2021-04-23 v1.1.4
    pump servo signal decoding implemented
2021-04-23 v1.1.4 – debug register added
    Debug mode by register implemented
2021-04-23 Debug mode register added
    - DEBUG_FLAG_REG added
    - BOOT_FLAG_REG address modified (0x40)
2021-04-23 Update for next PCB
2021-04-23 Downgrade to current version of PCB
2021-04-23 Update for next PCB version
2021-04-23 Integration Pastonomic
2021-04-23 derniere corrections
2021-04-26 MICHA pasteurisateur
2021-04-26 BOM and inventory updated
2021-04-26 principle diagram updated
2021-04-26 library used in eagle
2021-04-26 datasheet updated
2021-04-27 MICHA_nextPCB updated
    - analog switch added
    - zener and tvs for protection added
    - schottky diode deleted
    - error signal go through a bridge divider instead of a zener
2021-04-27 MICHA_nextPCB eagle files updated
    3.3V source of Mikro deleted
2021-04-27 BOM updated
2021-04-27 Eagle libraries updated
2021-04-28 MICHA.ino updated
2021-04-28 Update MICHA.py
    - management of debug_flag implemented
    - read_holding function added
2021-04-28 MICHAold.py updated (debug,speed step...)
2021-04-28 Inventory modified
2021-04-29 Btn & thermis zener replaced by Schottky
2021-04-29 Create SchottkyDiodes_SDM10M45SD.lbr
    Schottky SOT26 added
2021-04-29 Schottky added
2021-04-29 Better reverse
2021-04-29 Button diodes between resistor and capacitor
2021-04-29 Update 33 ohm resistor
2021-04-30 add jumpers for reserve and pump_relay
2021-04-30 Mikrobus footprint updated
2021-05-07 tNames updated
    Add +12V and +5V labels
2021-05-07 Components for MICHA v2 added
2021-05-07 Name updated
2021-05-08 Quantity updated
2021-05-10 Dissociation of V1 and V2 PCB
2021-05-10 Dissociation of the V1 and V2 PCB
2021-05-12 MAX4528CSA footprint updated
2021-05-12 Optocoupler footprint updated
2022-03-18 Micha v4 pour 1ere machine pilote
2022-03-18 Renommer les fichiers INO
2022-04-15 Nettoyage
    Remise au net
2022-04-22 mise à jour test unitaire
2022-04-22 ajout micha20
2022-04-22 Suppression des dossier MICHA et tests
2022-04-22 Nettoyage
    Suppression des fichiers en rapport avec le version 1 et autres
2022-04-22 Pré-nettoyage
2022-04-22 Nettoyage + uniformisation
2022-04-22 Mise à jours des BOM
2022-04-28 Ajout de MICHA41
2022-05-05 Pressure management
2022-12-22 Dernieres modifications
